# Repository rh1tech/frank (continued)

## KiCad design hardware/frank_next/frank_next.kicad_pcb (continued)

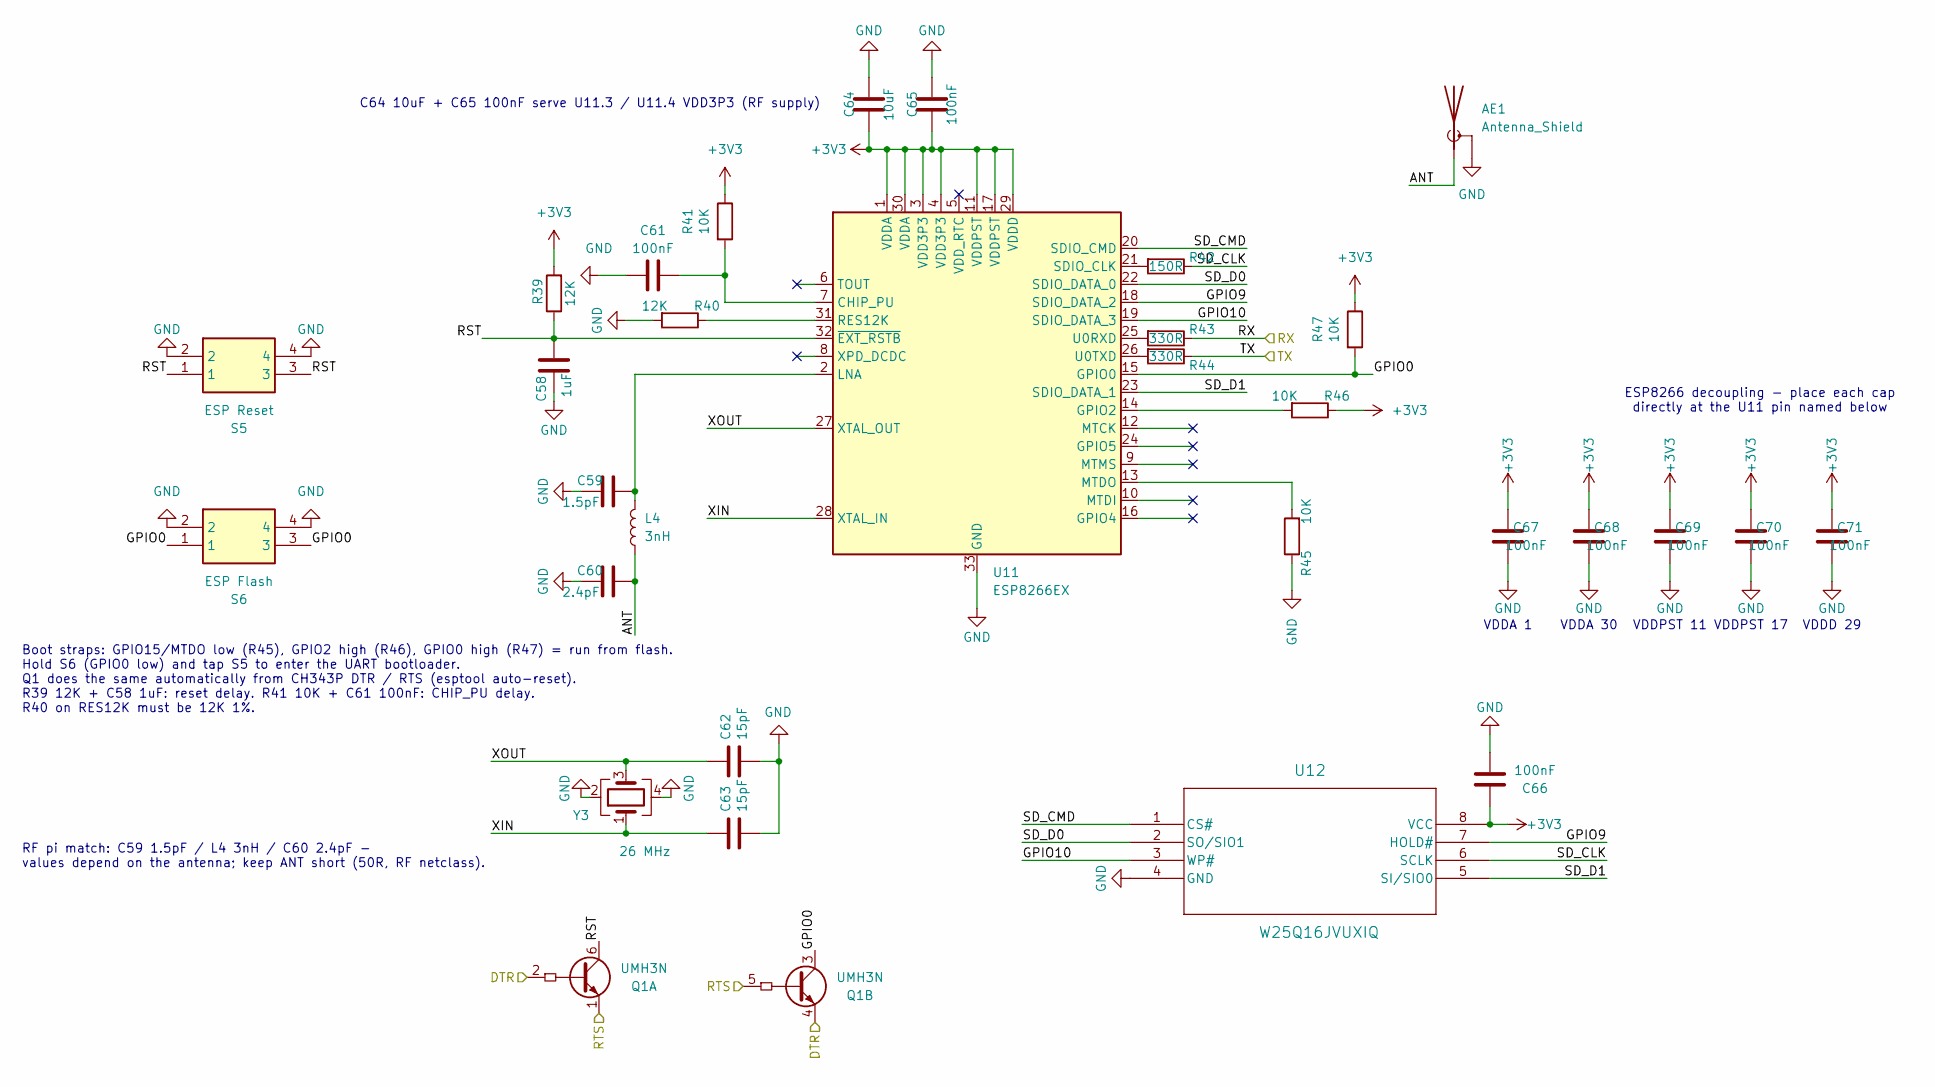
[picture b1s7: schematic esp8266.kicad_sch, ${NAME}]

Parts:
AE1: Antenna_Shield; Antenna_2.4GHz
C58: 1uF; C_0603_1608Metric; LCSC C5199872
C59: 1.5pF; C_0603_1608Metric; LCSC C1639
C60: 2.4pF; C_0603_1608Metric; LCSC C27741
C61, C65, C66, C67, C68, C69, C70, C71: 100nF; C_0603_1608Metric; LCSC C14663
C62, C63: 15pF; C_0603_1608Metric; LCSC C1644
C64: 10uF; C_0603_1608Metric; LCSC C96446
L4: 3nH; L_0603_1608Metric; LCSC C882466
Q1: UMH3N; SOT-363; LCSC C123008
R39, R40: 12K; R_0603_1608Metric; LCSC C22790
R41, R45, R46, R47: 10K; R_0603_1608Metric; LCSC C2906982
R42: 150R; R_0603_1608Metric; LCSC C22808
R43, R44: 330R; R_0603_1608Metric; LCSC C23138
S5: ESP Reset; Button_SMD_3x4x2mm; LCSC C55200587
S6: ESP Flash; Button_SMD_3x4x2mm; Mouser Part Number 611-KMR221G-LFS
U11: ESP8266EX; QFN-32-1EP_5x5mm_P0.5mm_EP3.45x3.45mm; LCSC C77967
U12: W25Q16JVUXIQ; USON-8-1EP_2x3mm_P0.5mm_EP0.2x1.6mm; LCSC C2843335
Y3: 26 MHz; Crystal_SMD_3225-4Pin_3.2x2.5mm; LCSC C15192

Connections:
+3V3: C64.2, C65.2, C66.1, C67.1, C68.1, C69.1, C70.1, C71.1, R39.2, R41.1, R46.1, R47.1, U11.1 (VDDA), U11.3 (VDD3P3), U11.4 (VDD3P3), U11.11 (VDDPST), U11.17 (VDDPST), U11.29 (VDDD), U11.30 (VDDA), U12.8 (VCC); also elsewhere on the board
/ESP8266/ANT: AE1.1 (A), C60.1, L4.1
/ESP8266/GPIO0: Q1.3 (C2), R47.2, S6.1, S6.3, U11.15 (GPIO0)
/ESP8266/GPIO9: U11.18 (SDIO_DATA_2), U12.7 (HOLD#)
/ESP8266/GPIO10: U11.19 (SDIO_DATA_3), U12.3 (WP#)
/ESP8266/RST: C58.1, Q1.6 (C1), R39.1, S5.1, S5.3, U11.32 (~EXT_RSTB)
/ESP8266/RX: R43.1; also elsewhere on the board
/ESP8266/SD_CLK: R42.1, U12.6 (SCLK)
/ESP8266/SD_CMD: U11.20 (SDIO_CMD), U12.1 (CS#)
/ESP8266/SD_D0: U11.22 (SDIO_DATA_0), U12.2 (SO/SIO1)
/ESP8266/SD_D1: U11.23 (SDIO_DATA_1), U12.5 (SI/SIO0)
/ESP8266/TX: R44.1; also elsewhere on the board
/ESP8266/XIN: C63.1, U11.28 (XTAL_IN), Y3.1
/ESP8266/XOUT: C62.1, U11.27 (XTAL_OUT), Y3.3
/ESP_DTR: Q1.2 (B1), Q1.4 (E2); also elsewhere on the board
/ESP_RTS: Q1.1 (E1), Q1.5 (B2); also elsewhere on the board
GND: AE1.2 (Shield), C58.2, C59.2, C60.2, C61.2, C62.2, C63.2, C64.1, C65.1, C66.2, C67.2, C68.2, C69.2, C70.2, C71.2, R40.2, R45.1, S5.2, S5.4, S6.2, S6.4, U11.33 (GND), U12.4 (GND), Y3.2, Y3.4; also elsewhere on the board
unnamed: C61.1, R41.2, U11.7 (CHIP_PU)
unnamed: R46.2, U11.14 (GPIO2)
unnamed: C59.1, L4.2, U11.2 (LNA)
unnamed: R45.2, U11.13 (MTDO)
unnamed: R40.1, U11.31 (RES12K)
unnamed: R42.2, U11.21 (SDIO_CLK)
unnamed: R43.2, U11.25 (U0RXD)
unnamed: R44.2, U11.26 (U0TXD)

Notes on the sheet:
VDDD 29
VDDA 30
C64 10uF + C65 100nF serve U11.3 / U11.4 VDD3P3 (RF supply)
ESP8266 decoupling - place each cap directly at the U11 pin named below
VDDPST 17
RF pi match: C59 1.5pF / L4 3nH / C60 2.4pF - values depend on the antenna; keep ANT short (50R, RF netclass).
Boot straps: GPIO15/MTDO low (R45), GPIO2 high (R46), GPIO0 high (R47) = run from flash. Hold S6 (GPIO0 low) and tap S5 to enter the UART bootloader. Q1 does the same automatically from CH343P DTR / RTS (esptool auto-reset). R39 12K + C58 1uF: reset delay. R41 10K + C61 100nF: CHIP_PU delay. R40 on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
VDDPST 11
VDDA 1

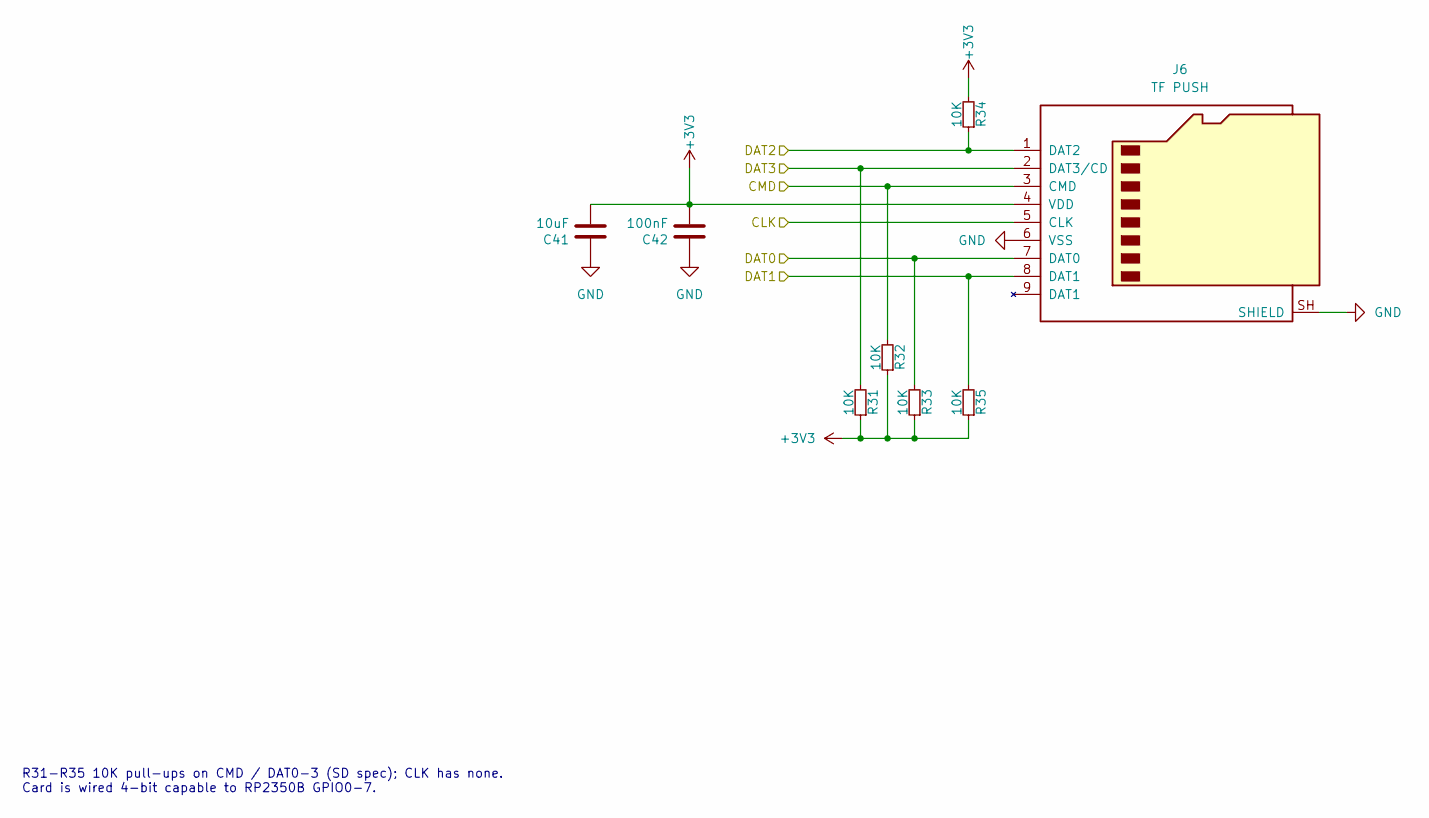
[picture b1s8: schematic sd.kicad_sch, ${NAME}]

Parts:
C41: 10uF; C_0603_1608Metric; LCSC C96446
C42: 100nF; C_0603_1608Metric; LCSC C14663
J6: TF PUSH; MicroSD_SMD_Long; LCSC C393941
R31, R32, R33, R34, R35: 10K; R_0603_1608Metric; LCSC C2906982

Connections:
+3V3: C41.2, C42.2, J6.4 (VDD), R31.1, R32.1, R33.1, R34.2, R35.1; also elsewhere on the board
/SD/CD_DAT3/GPIO7: J6.2 (DAT3/CD), R31.2; also elsewhere on the board
/SD/CLK/GPIO1: J6.5 (CLK); also elsewhere on the board
/SD/CMD/GPIO0: J6.3 (CMD), R32.2; also elsewhere on the board
/SD/DAT0/GPIO4: J6.7 (DAT0), R33.2; also elsewhere on the board
/SD/DAT1/GPIO5: J6.8 (DAT1), R35.2; also elsewhere on the board
/SD/DAT2/GPIO6: J6.1 (DAT2), R34.1; also elsewhere on the board
GND: C41.1, C42.1, J6.6 (VSS), J6.SH (SHIELD); also elsewhere on the board

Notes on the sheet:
R31-R35 10K pull-ups on CMD / DAT0-3 (SD spec); CLK has none. Card is wired 4-bit capable to RP2350B GPIO0-7.

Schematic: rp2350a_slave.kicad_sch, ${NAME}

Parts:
C21, C26, C29, C31, C32, C33, C34, C35, C36, C37, C38, C39: 100nF; C_0603_1608Metric; LCSC C14663
C22, C25, C27, C28: 4.7uF; C_0603_1608Metric; LCSC C5360844
C23, C24: 15pF; C_0603_1608Metric; LCSC C1644
C30, C40: 1uF; C_0603_1608Metric; LCSC C5199872
D2: 1N4148WS; D_SOD-323; LCSC C2128
J4: Debug; JST_SH_1x03_P1.00mm_Vertical; LCSC C160389
J5: UART; JST_SH_1x03_P1.00mm_Vertical; LCSC C160389
L2: 3.3µH; L_AOTA-B201610_2.0x1.6mm; LCSC C42411119
LD1: Blue; LED_0603_1608Metric; LCSC C965807
LD2: WS2812B-2020; LED_WS2812B-2020_PLCC4_2.0x2.0mm; LCSC C965555
R19, R30: 10K; R_0603_1608Metric; LCSC C2906982
R20, R22, R28: 1K; R_0603_1608Metric; LCSC C21190
R21: 33R; R_0603_1608Metric; LCSC C23140
R23: 0R; R_0603_1608Metric; LCSC C21189
R24: 2.2K; R_0603_1608Metric; LCSC C4190
R25, R26: 27R; R_0603_1608Metric; LCSC C25190
R27: 4.7K; R_0603_1608Metric; LCSC C23162
R29: 330R; R_0603_1608Metric; LCSC C23138
S3: RP Boot; Button_SMD_3x4x2mm; Mouser Part Number 611-KMR221G-LFS; LCSC C55200587
S4: RP Reset; Button_SMD_3x4x2mm; Mouser Part Number 611-KMR221G-LFS; LCSC C55200587
U4: W25Q128JVPIQ; WSON-8-1EP_6x5mm_P1.27mm_EP3.45x4.35mm; Mouser Part Number 454-W25Q128JVPIQ; LCSC C190862
U5: RP2350; QFN-60-1EP_7x7mm_P0.4mm_EP3.4x3.4mm; LCSC C42411118
U6, U8: APS6404L-3SQR-ZR; PSON50P200X300X50-9N; PARTREV 2.3; LCSC C3040877
U7: SN74LVC1G3157DBVR; SOT-23-6; LCSC C10426
Y2: 12 MHz; Crystal_SMD_3225-4Pin_3.2x2.5mm; LCSC C20625731

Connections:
+1V1_A: C25.1, C26.1, C28.1, C29.1, L2.1, U5.6 (DVDD), U5.23 (DVDD), U5.39 (DVDD), U5.50 (VREG_FB)
+3V3: C21.1, C22.1, C30.2, C31.1, C32.1, C33.1, C34.1, C35.1, C36.1, C37.1, C39.1, C40.1, R19.2, R21.1, R24.2, R30.1, U4.8 (VCC), U5.1 (IOVDD), U5.11 (IOVDD), U5.20 (IOVDD), U5.30 (IOVDD), U5.38 (IOVDD), U5.44 (ADC_AVDD), U5.45 (IOVDD), U5.49 (VREG_VIN), U5.53 (USB_OTP_VDD), U5.54 (QSPI_IOVDD), U6.8 (VDD), U7.5 (VCC), U8.8 (VDD); also elsewhere on the board
/RP2350A/BOOT: R22.2, S3.1, S3.3
/RP2350A/D+: R25.1; also elsewhere on the board
/RP2350A/D-: R26.1; also elsewhere on the board
/RP2350A/GPIO0: U5.2 (GPIO0), U7.4 (A)
/RP2350A/GPIO9: U5.13 (GPIO9); also elsewhere on the board
/RP2350A/GPIO24/UART_1: J5.1, U5.36 (GPIO24)
/RP2350A/GPIO25/UART_3: J5.3, U5.37 (GPIO25)
/RP2350A/GPIO28: R27.1, U5.42 (GPIO28_ADC2), U7.6 (S)
/RP2350A/GPIO29: U5.43 (GPIO29_ADC3)
/RP2350A/PSRAM0_CS: R24.1, U6.1 (~CE), U7.3 (B1)
/RP2350A/PSRAM1_CS: R30.2, U7.1 (B2), U8.1 (~CE)
/RP2350A/QSPI_SCLK: U4.6 (CLK), U5.56 (QSPI_SCLK), U6.6 (SCLK), U8.6 (SCLK)
/RP2350A/QSPI_SD0: U4.5 (DI_(IO0)), U5.57 (QSPI_SD0), U6.5 (SI/SIO(0)), U8.5 (SI/SIO(0))
/RP2350A/QSPI_SD1: U4.2 (DO_(IO1)), U5.59 (QSPI_SD1), U6.2 (SO/SIO(1)), U8.2 (SO/SIO(1))
/RP2350A/QSPI_SD2: U4.3 (~WP_(IO2)), U5.58 (QSPI_SD2), U6.3 (SIO(2)), U8.3 (SIO(2))
/RP2350A/QSPI_SD3: U4.7 (~HOLD_OR_/RESET_(IO3)), U5.55 (QSPI_SD3), U6.7 (SIO(3)), U8.7 (SIO(3))
/RP2350A/QSPI_SS: R22.1, R23.1, U5.60 (QSPI_SS)
/RP2350A/SWCLK: J4.3, U5.24 (SWCLK)
/RP2350A/SWD: J4.1, U5.25 (SWD)
/RP2350A/VREG_AVDD: C27.1, R21.2, U5.46 (VREG_AVDD)
/RP2350A/VREG_LX: L2.2, U5.48 (VREG_LX)
/RP2350A/XIN: C23.1, U5.21 (XIN), Y2.3
/RP2350A/XOUT: R20.2, U5.22 (XOUT)
/RP2350/20B/1A/D0: U5.3 (GPIO1); also elsewhere on the board
/RP2350/21B/2A/D1: U5.4 (GPIO2); also elsewhere on the board
/RP2350/22B/3A/D2: U5.5 (GPIO3); also elsewhere on the board
/RP2350/23B/4A/D3: U5.7 (GPIO4); also elsewhere on the board
/RP2350/24B/5A/D4: U5.8 (GPIO5); also elsewhere on the board
/RP2350/25B/6A/D5: U5.9 (GPIO6); also elsewhere on the board
/RP2350/26B/7A/D6: U5.10 (GPIO7); also elsewhere on the board
/RP2350/27B/8A/D7: U5.12 (GPIO8); also elsewhere on the board
/RP2350/29B/10A/VALID: U5.14 (GPIO10); also elsewhere on the board
/RP2350/30B/11A/D0: U5.15 (GPIO11); also elsewhere on the board
/RP2350/31B/12A/D1: U5.16 (GPIO12); also elsewhere on the board
/RP2350/32B/13A/D2: U5.17 (GPIO13); also elsewhere on the board
/RP2350/33B/14A/D3: U5.18 (GPIO14); also elsewhere on the board
/RP2350/34B/15A/D4: U5.19 (GPIO15); also elsewhere on the board
/RP2350/35B/16A/D5: U5.27 (GPIO16); also elsewhere on the board
/RP2350/36B/17A/D6: U5.28 (GPIO17); also elsewhere on the board
/RP2350/37B/18A/D7: U5.29 (GPIO18); also elsewhere on the board
/RP2350/38B/19A/CLK: U5.31 (GPIO19); also elsewhere on the board
/RP2350/39B/20A/VALID: U5.32 (GPIO20); also elsewhere on the board
/RP2350/40B/21A/FS: U5.33 (GPIO21); also elsewhere on the board
/RP2350/41B/22A/DB_MS: U5.34 (GPIO22); also elsewhere on the board
/RP2350/42B/23A/DB_SM: U5.35 (GPIO23); also elsewhere on the board
/RP2350/43B/RUNA/SR: S4.1, S4.3, U5.26 (RUN); also elsewhere on the board
GND: C21.2, C22.2, C23.2, C24.2, C25.2, C26.2, C27.2, C28.2, C29.2, C30.1, C31.2, C32.2, C33.2, C34.2, C35.2, C36.2, C37.2, C38.2, C39.2, C40.2, J4.2, J5.2, LD1.1 (K), LD2.2 (VSS), R27.2, S3.2, S3.4, S4.2, S4.4, U4.4 (GND_1), U4.9 (GND_2), U5.47 (VREG_PGND), U5.61 (GND), U6.4 (VSS), U6.9 (EXP), U7.2 (GND), U8.4 (VSS), U8.9 (EXP), Y2.2, Y2.4; also elsewhere on the board
unnamed: C24.1, R20.1, Y2.1
unnamed: C38.1, D2.1 (K), LD2.4 (VDD)
unnamed: LD1.2 (A), R28.1
unnamed: LD2.3 (DIN), R29.1
unnamed: R19.1, R23.2, U4.1 (~CS)
unnamed: R28.2, U5.40 (GPIO26_ADC0)
unnamed: R29.2, U5.41 (GPIO27_ADC1)
unnamed: R26.2, U5.51 (USB_DM)
unnamed: R25.2, U5.52 (USB_DP)
VBUS: D2.2 (A); also elsewhere on the board

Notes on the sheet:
44+45
LD2 WS2812B is powered from VBUS via D2 (~4.4 V), so the 3.3 V DIN still meets its VIH. R29 330R: data series.
PSRAM bank: GPIO28 L (default, R27 4.7k) = U6, H = U8. Flush XIP cache before switching banks.
Core supply: L2 3.3uH + C22 / C25 4.7uF = on-chip buck, keep the loop short. R21 33R + C27 4.7uF filter VREG_AVDD.
Make sure these are close to RP2350
S3 BOOT: QSPI_SS low via R22 1K. RUN comes from RP2350B (root sheet).
53+54

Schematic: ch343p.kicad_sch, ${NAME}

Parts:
C97, C98, C99: 100nF; C_0603_1608Metric; LCSC C14663
LD4: Orange; LED_0603_1608Metric; LCSC C965800
R70: 1K; R_0603_1608Metric; LCSC C21190
U22: CH343P; WCH_QFN-16-1EP_3x3mm_P0.5mm_EP1.8x1.8mm; LCSC C2846043

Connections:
+3V3: C99.2, R70.2, U22.1 (VIO); also elsewhere on the board
/CH343P/UD+: U22.7 (UD+); also elsewhere on the board
/CH343P/UD-: U22.8 (UD-); also elsewhere on the board
/ESP_DTR: U22.12 (~DTR); also elsewhere on the board
/ESP_RTS: U22.13 (~RTS); also elsewhere on the board
/TTL_RXD: U22.5 (RXD); also elsewhere on the board
/TTL_TXD: U22.4 (TXD); also elsewhere on the board
GND: C97.1, C98.1, C99.1, U22.2 (GND), U22.17 (GND_EPAD); also elsewhere on the board
unnamed: LD4.2 (A), R70.1
unnamed: LD4.1 (K), U22.10 (~ACT)
unnamed: C98.2, U22.6 (V3_{OUT})
VBUS: C97.2, U22.3 (VDD5), U22.9 (VBUS); also elsewhere on the board

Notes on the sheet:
CH343P USB-UART: reached from J11 when USB_SEL is low. Talks to the ESP8266 through the ESP Mux (UART_SEL low); DTR / RTS drive the ESP8266 auto-program transistors (Q1). LD4: activity LED.

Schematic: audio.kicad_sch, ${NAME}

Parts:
C43, C44, C50, C53, C55: 100nF; C_0603_1608Metric; LCSC C14663
C45, C46, C49, C51, C52, C54, C56: 10uF; C_0603_1608Metric; LCSC C96446
C47, C48: 100uF; C_1206_3216Metric; LCSC C7432784
C57: 1uF; C_0603_1608Metric; LCSC C5199872
J7: PJ-320D; AudioJack_3.5mm_PJ320D_AudioOut; LCSC C431535
J8: Speaker; JST_GH_1x02_P1.25mm; LCSC C114130
L3: 330R 2A; L_0805_2012Metric; LCSC C76819
R36, R37: 4.7K; R_0603_1608Metric; LCSC C23162
R38: 10K; R_0603_1608Metric; LCSC C2906982
U9: TLV320DAC3100IRHBR; Mouser Part Number 595-V320DAC3100IRHBR; LCSC C179677
U10: XC6206P182MR-G; Mouser Part Number 865-XC6206P182MR-G; LCSC C347373

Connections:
+1V8: C44.2, C56.2, U9.3 (DVDD), U10.2 (VOUT)
+3V3: C43.1, C45.1, C49.2, C50.2, C51.2, C53.2, C57.2, R36.2, R37.2, R38.2, U9.2 (IOVDD), U9.17 (AVDD), U9.28 (HPVDD), U10.3 (VIN); also elsewhere on the board
/Audio/+5V_SPK: C52.2, C54.2, C55.2, L3.1, U9.21 (SPKVDD_1), U9.24 (SPKVDD_2)
/Audio/SPKM: J8.2, U9.19 (SPKM_1), U9.23 (SPKM_2)
/Audio/SPKP: J8.1, U9.22 (SPKP_1), U9.26 (SPKP_2)
/GPIO2/SDA: R37.1, U9.9 (SDA); also elsewhere on the board
/GPIO3/SCL: R36.1, U9.10 (SCL); also elsewhere on the board
/GPIO8/MCLK: U9.8 (MCLK); also elsewhere on the board
/GPIO9/BCLK: U9.7 (BCLK); also elsewhere on the board
/GPIO10/WCLK: U9.6 (WCLK); also elsewhere on the board
/GPIO11/DIN: U9.5 (DIN); also elsewhere on the board
GND: C43.2, C44.1, C45.2, C46.2, C49.1, C50.1, C51.1, C52.1, C53.1, C54.1, C55.1, C56.1, C57.1, J7.S, U9.1 (IOVSS), U9.16 (AVSS), U9.18 (DVSS), U9.20 (SPKVSS_1), U9.25 (SPKVSS_2), U9.29 (HPVSS), U9.33 (EP), U10.1 (VSS); also elsewhere on the board
unnamed: C47.1, J7.R
unnamed: C48.1, J7.T
unnamed: C48.2, U9.27 (HPL)
unnamed: C47.2, U9.30 (HPR)
unnamed: C46.1, R38.1, U9.31 (~RESET)
VBUS: L3.2; also elsewhere on the board

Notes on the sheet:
U9 TLV320DAC3100, I2C address 0x18 on GPIO2 / GPIO3 (shared with RTC U13, R36 / R37 4.7K pull-ups). I2S: MCLK GPIO8, BCLK GPIO9, WCLK GPIO10, DIN GPIO11. DVDD 1.8 V from U10 XC6206 LDO. SPKVDD from VBUS through L3 ferrite; C55 / C52 / C54 at the SPKVDD pins. Headphone HPL / HPR AC-coupled by C47 / 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

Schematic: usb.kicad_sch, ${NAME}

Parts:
C76, C79, C80, C86, C88: 100nF; C_0603_1608Metric; LCSC C14663
C77, C78: 100uF; CP_Elec_6.3x6.0; LCSC C19270701
C81, C82, C83, C85, C87, C89, C91, C92, C93: 10uF; C_0603_1608Metric; LCSC C96446
C84: 47nF; C_0603_1608Metric; LCSC C1622
C90: 1uF; C_0603_1608Metric; LCSC C5199872
C94, C95: 12pF; C_0603_1608Metric; LCSC C107034
C96: 22pF; C_0603_1608Metric; LCSC C1653
J10, J11: USB4215-03-A; USB_C_Receptacle; LCSC C37616412
JP4: USB Debug; SolderJumper-2_P1.3mm_Open_RoundedPad1.0x1.5mm
JP5: PWR Debug; SolderJumper-2_P1.3mm_Open_RoundedPad1.0x1.5mm
L5: 330R 2A; L_0805_2012Metric; LCSC C76819
L6: 2.2uH; L_Cenker_CKCS3015; LCSC C167747
LD3: Green; LED_0603_1608Metric; LCSC C965804
R55, R65: 10K; R_0603_1608Metric; LCSC C2906982
R56, R57, R58, R59: 5.1K; R_0603_1608Metric; LCSC C23186
R60: 300K; R_0603_1608Metric; LCSC C23024
R61, R64, R68: 100K; R_0603_1608Metric; LCSC C25803
R62: 1M; R_0603_1608Metric; LCSC C22935; not fitted
R63: 1K; R_0603_1608Metric; LCSC C21190
R66, R69: 22K; R_0603_1608Metric; LCSC C31850
R67: 4.7K; R_0603_1608Metric; LCSC C23162; not fitted
S7: SS12D01; Switch_Slide_SS12D00; Mouser Part Number 611-SK12D07VG3NS
S8: SK12D07VG3NS; Switch_Slide_SK12D07VG3NS_PWR; Mouser Part Number 611-SK12D07VG3NS; LCSC C431547
U14, U19: TS3USB221RSER; UQFN-10; LCSC C130085
U15, U16: TPD4S012DRYR; Mouser Part Number 595-TPD4S012DRYR; LCSC C96506
U17: TPS2116DRL; SOT-583-8; LCSC C3235557
U18: AO3401A; SOT-23-3L_AOS; LCSC C15127
U20: SY8089AAAC; SOT-23-5; LCSC C78988
U21: CH334F; QFN-24-1EP_4x4mm_P0.5mm_EP2.7x2.7mm; LCSC C5187527
Y4: 12 MHz; Crystal_SMD_3225-4Pin_3.2x2.5mm; LCSC C20625731

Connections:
+3V3: C76.1, C86.2, C91.1, C92.1, C96.1, JP4.1 (A), L6.1, R55.1, R63.2, R68.1, S7.2, U14.10 (VCC), U19.10 (VCC); also elsewhere on the board
/CH343P/UD+: U14.1 (1D+); also elsewhere on the board
/CH343P/UD-: U14.2 (1D-); also elsewhere on the board
/RP2350A/D+: U14.3 (2D+); also elsewhere on the board
/RP2350A/D-: U14.4 (2D-); also elsewhere on the board
/RP2350B/D+: U19.8 (D+); also elsewhere on the board
/RP2350B/D-: U19.7 (D-); also elsewhere on the board
/USB/+5V_BUCK: C85.1, C87.1, C88.1, L5.2, U20.1 (EN), U20.4 (IN)
/USB/D2+: J10.6 (DP1), J10.8 (DP2), U15.1 (D+), U19.1 (1D+)
/USB/D2-: J10.5 (DN2), J10.7 (DN1), U15.2 (D-_), U19.2 (1D-)
/USB/DH+: U19.3 (2D+), U21.15 (DPU+)
/USB/DH-: U19.4 (2D-), U21.14 (DMU-)
/USB/DS1+: U21.12 (DP1+); also elsewhere on the board
/USB/DS1-: U21.11 (DM1-); also elsewhere on the board
/USB/DS2+: U21.10 (DP2+); also elsewhere on the board
/USB/DS2-: U21.9 (DM2-); also elsewhere on the board
/USB/DS3+: U21.8 (DP3+); also elsewhere on the board
/USB/DS3-: U21.7 (DM3-); also elsewhere on the board
/USB/OVCUR: U21.1 (~OVCUR); also elsewhere on the board
/USB/PWREN: U21.24 (~PWREN); also elsewhere on the board
/USB/S: JP4.2 (B), R65.2, S7.3, U19.9 (S)
/USB/ST: R62.2, U17.8 (ST)
/USB/USBC_D+: J11.6 (DP1), J11.8 (DP2), U14.8 (D+), U16.1 (D+)
/USB/USBC_D-: J11.5 (DN2), J11.7 (DN1), U14.7 (D-), U16.2 (D-_)
/USB/VBUS_IN: C83.1, R64.2, U17.2 (VOUT), U17.7 (VOUT), U18.2 (S)
/USB/VBUS_IN1: C79.2, C81.2, J11.2 (VBUS), J11.11 (VBUS), R60.2, U16.6 (VBUS), U17.3 (VIN1), U17.5 (MODE)
/USB/VBUS_IN2: C80.2, C82.2, J10.2 (VBUS), J10.11 (VBUS), U15.6 (VBUS), U17.6 (VIN2)
/USB/VDD33: C89.2, C90.2, U21.20 (VDD33_{LDO})
/USB/XTAL_N: C94.1, U21.3 (XO), Y4.3
/USB/XTAL_P: C95.1, U21.4 (XI), Y4.1
/USB_SEL: R55.2, U14.9 (S); also elsewhere on the board
GND: C76.2, C77.2, C78.2, C79.1, C80.1, C81.1, C82.1, C83.2, C85.2, C86.1, C87.2, C88.2, C89.1, C90.1, C91.2, C92.2, C93.1, C94.2, C95.2, J10.1 (GND), J10.12 (GND), J10.13 (SHIELD), J11.1 (GND), J11.12 (GND), J11.13 (SHIELD), JP5.1 (A), LD3.1 (K), R56.1, R57.1, R58.1, R59.1, R61.1, R65.1, R67.2, R69.2, S8.2, U14.5 (GND), U14.6 (~OE), U15.4 (GND), U16.4 (GND), U17.1 (GND), U19.5 (GND), U19.6 (~OE), U20.2 (GND), U21.25 (GND), Y4.2, Y4.4; also elsewhere on the board
unnamed: J10.4 (CC1), R56.2
unnamed: J10.10 (CC2), R57.2
unnamed: J11.4 (CC1), R58.2
unnamed: J11.10 (CC2), R59.2
unnamed: JP5.2 (B), R66.2, S8.3
unnamed: LD3.2 (A), R63.1
unnamed: R60.1, R61.2, R62.1, U17.4 (PR1)
unnamed: C84.1, R64.1, R66.1, U18.1 (G)
unnamed: C96.2, R68.2, R69.1, U20.5 (FB)
unnamed: L6.2, U20.3 (LX)
unnamed: R67.1, U21.18 (PSELF)
VBUS: C77.1, C78.1, C84.2, C93.2, L5.1, U18.3 (D), U21.19 (V5); also elsewhere on the board

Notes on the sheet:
USB data: U14 (USB_SEL): J11 -> RP2350A (H) or CH343P (L). U19 (S7 USB FUNC, JP4 forces H): RP2350B -> J10 (L, device) or CH334F hub upstream -> USB-A ports (H, host).
Power path: J11 (VIN1) / J10 (VIN2) -> U17 TPS2116. J11 is preferred while its VBUS is above ~4 V (R60 / R61 on PR1, MODE tied to VIN1). R62: DNP. S8 -> U18 AO3401A P-FET: R64 holds it off, S8 pulls the gate low via R66, C84 = soft start. JP5 bypasses S8. VBUS -> L5 ferrite -> U20 SY8089 buck: 3V3 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
USB-A shared VBUS bulk: C77 + C78 = 200 uF USB 2.0 7.2.4.1: >= 120 uF per hub, may be shared DMBJ JBLM2101M016C058RTM (LCSC C19270701) 100 uF 16 V aluminium polymer, ESR 40 mOhm
5.1K CC pull-downs (Rd): both USB-C ports are sinks

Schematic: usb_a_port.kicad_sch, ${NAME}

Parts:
C100: 100nF; C_0603_1608Metric; LCSC C14663
C101: 10uF; C_0603_1608Metric; LCSC C96446
J12: AF 10.0 HC6.3; USB_A_Short; LCSC C456017
R71: 100K; R_0603_1608Metric; LCSC C25803
U23: TPD4S012DRYR; Mouser Part Number 595-TPD4S012DRYR; LCSC C96506
U24: CH217A; SOT-23-6; LCSC C54973763

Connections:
/USB/DS1+: J12.3 (D+), U23.1 (D+); also elsewhere on the board
/USB/DS1-: J12.2 (D-), U23.2 (D-_); also elsewhere on the board
/USB/OVCUR: U24.3 (FLAG#); also elsewhere on the board
/USB/PWREN: U24.4 (EN#); also elsewhere on the board
/USB/USB A Port 1/VBUS_P: C100.1, J12.1 (VBUS), U23.6 (VBUS), U24.1 (VOUT)
GND: C100.2, C101.1, J12.4 (GND), J12.5 (Shield), R71.1, U23.4 (GND), U24.2 (GND); also elsewhere on the board
unnamed: R71.2, U24.5 (ISET)
VBUS: C101.2, U24.6 (VIN); also elsewhere on the board

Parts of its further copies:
C102, C104: 100nF; C_0603_1608Metric; LCSC C14663
C103, C105: 10uF; C_0603_1608Metric; LCSC C96446
J13, J14: AF 10.0 HC6.3; USB_A_Short; LCSC C456017
R72, R73: 100K; R_0603_1608Metric; LCSC C25803
U25, U27: TPD4S012DRYR; Mouser Part Number 595-TPD4S012DRYR; LCSC C96506
U26, U28: CH217A; SOT-23-6; LCSC C54973763

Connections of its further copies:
/USB/DS2+: J13.3 (D+), U25.1 (D+); also elsewhere on the board
/USB/DS2-: J13.2 (D-), U25.2 (D-_); also elsewhere on the board
/USB/DS3+: J14.3 (D+), U27.1 (D+); also elsewhere on the board
/USB/DS3-: J14.2 (D-), U27.2 (D-_); also elsewhere on the board
/USB/OVCUR: U26.3 (FLAG#), U28.3 (FLAG#); also elsewhere on the board
/USB/PWREN: U26.4 (EN#), U28.4 (EN#); also elsewhere on the board
/USB/USB A Port 2/VBUS_P: C102.1, J13.1 (VBUS), U25.6 (VBUS), U26.1 (VOUT)
/USB/USB A Port 3/VBUS_P: C104.1, J14.1 (VBUS), U27.6 (VBUS), U28.1 (VOUT)
GND: C102.2, C103.1, C104.2, C105.1, J13.4 (GND), J13.5 (Shield), J14.4 (GND), J14.5 (Shield), R72.1, R73.1, U25.4 (GND), U26.2 (GND), U27.4 (GND), U28.2 (GND); also elsewhere on the board
unnamed: R72.2, U26.5 (ISET)
unnamed: R73.2, U28.5 (ISET)
VBUS: C103.2, C105.2, U26.6 (VIN), U28.6 (VIN); also elsewhere on the board

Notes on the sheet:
CH217A: current-limited VBUS switch for this port, enabled by the hub PWREN, over-current reported on OVCUR. The ISET resistor sets the limit. TPD4S012: ESD protection for D+ / D- / VBUS.

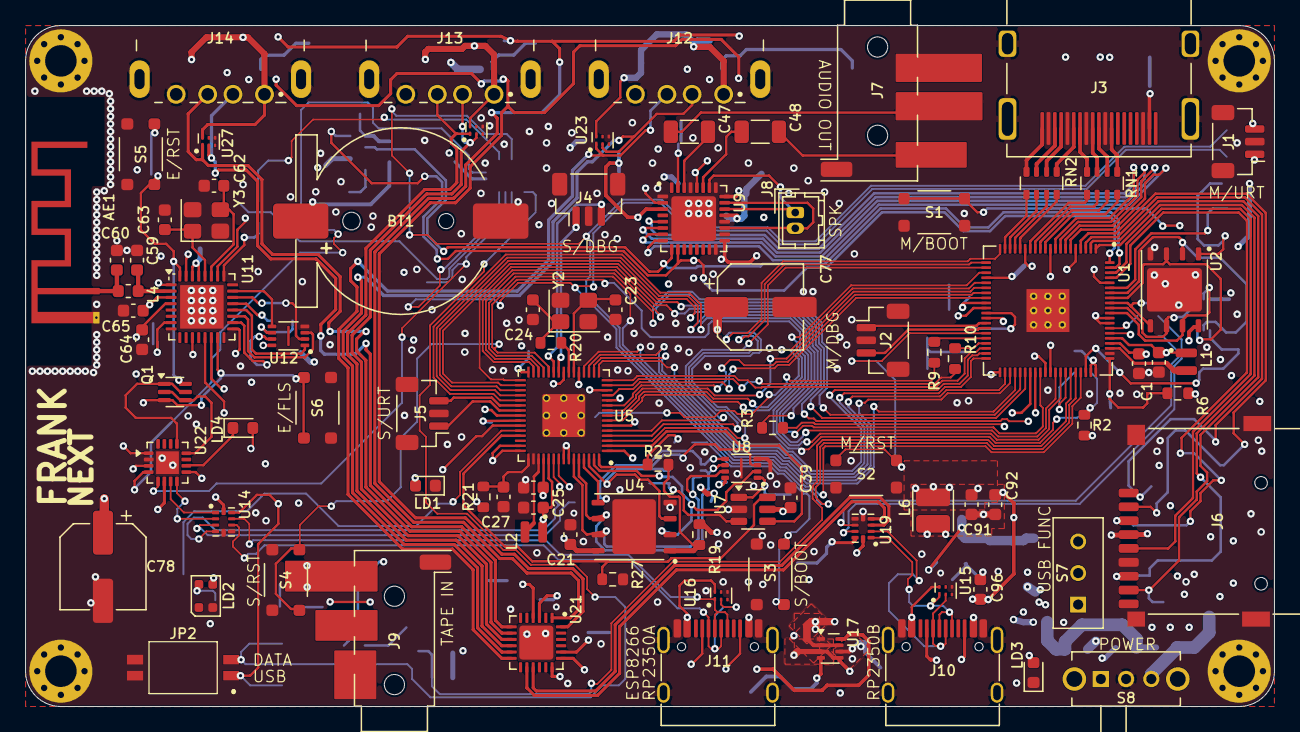
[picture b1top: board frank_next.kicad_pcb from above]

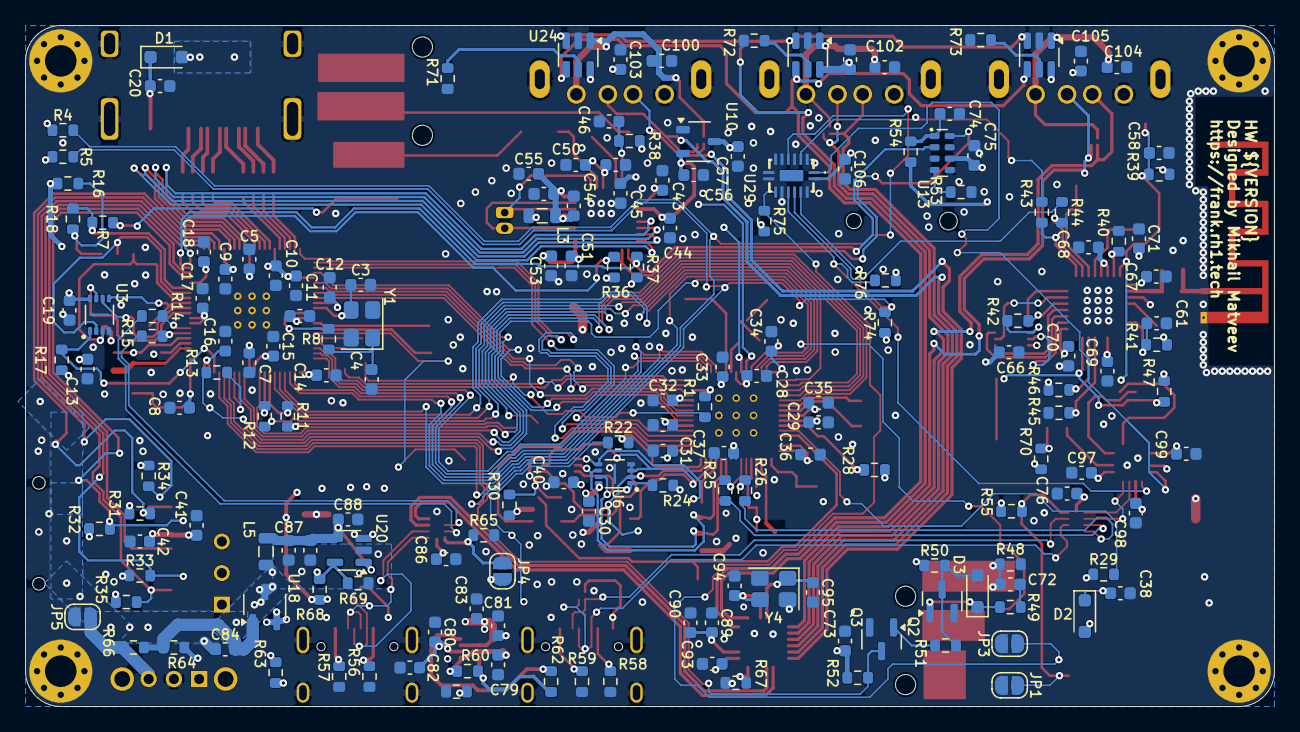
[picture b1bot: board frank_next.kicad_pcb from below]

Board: 4 copper layers, 99.0 x 54.0 mm, 266 parts (173 on the bottom side), 210 nets.

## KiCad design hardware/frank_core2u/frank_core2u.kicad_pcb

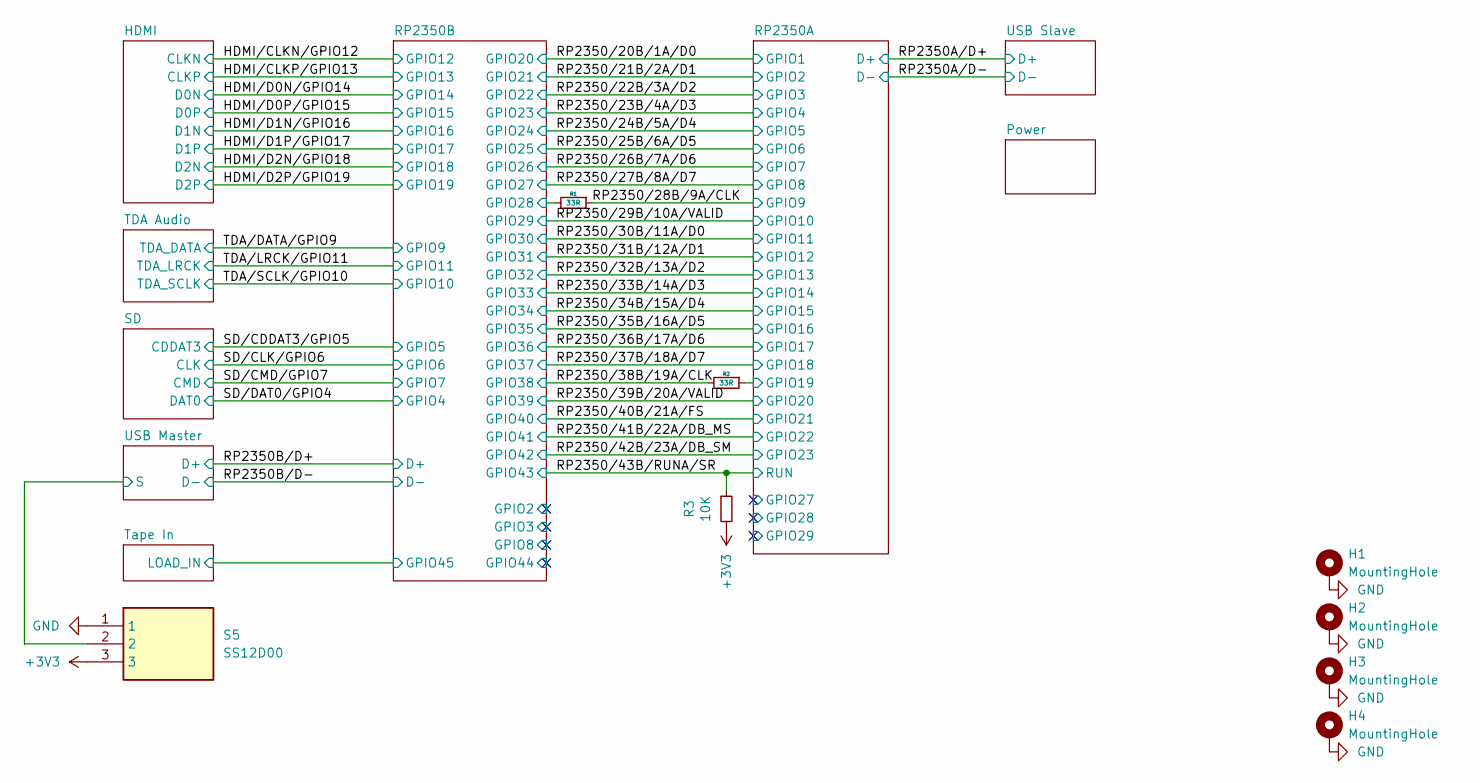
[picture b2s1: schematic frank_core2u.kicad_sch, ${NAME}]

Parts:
H1, H2, H3, H4: MountingHole; MountingHole_2.5mm_Pad_Via
R1, R2: 33R; R_0603_1608Metric
R3: 10K; R_0603_1608Metric
S5: SS12D00; Switch_Slide_SS12D00; Mouser Part Number 611-SK12D07VG3NS

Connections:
+3V3: R3.2, S5.3; also elsewhere on the board
/RP2350A/GPIO19: R2.1; also elsewhere on the board
/RP2350B/GPIO28: R1.2; also elsewhere on the board
/RP2350/28B/9A/CLK: R1.1; also elsewhere on the board
/RP2350/38B/19A/CLK: R2.2; also elsewhere on the board
/RP2350/43B/RUNA/SR: R3.1; also elsewhere on the board
/USB Master/S: S5.2; also elsewhere on the board
GND: H1.1 (1_1), H2.1 (1_1), H3.1 (1_1), H4.1 (1_1), S5.1; also elsewhere on the board

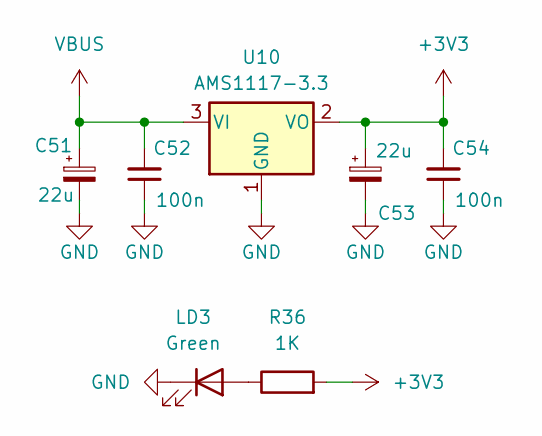
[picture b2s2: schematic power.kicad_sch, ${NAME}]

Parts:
C51, C53: 22u; CP_EIA-3528-12_Kemet-T
C52, C54: 100n; C_0603_1608Metric
LD3: Green; LED_0603_1608Metric
R36: 1K; R_0603_1608Metric
U10: AMS1117-3.3; SOT-89-3

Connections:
+3V3: C53.1, C54.2, R36.2, U10.2 (VO); also elsewhere on the board
GND: C51.2, C52.1, C53.2, C54.1, LD3.1 (K), U10.1 (GND); also elsewhere on the board
unnamed: LD3.2 (A), R36.1
VBUS: C51.1, C52.2, U10.3 (VI); also elsewhere on the board

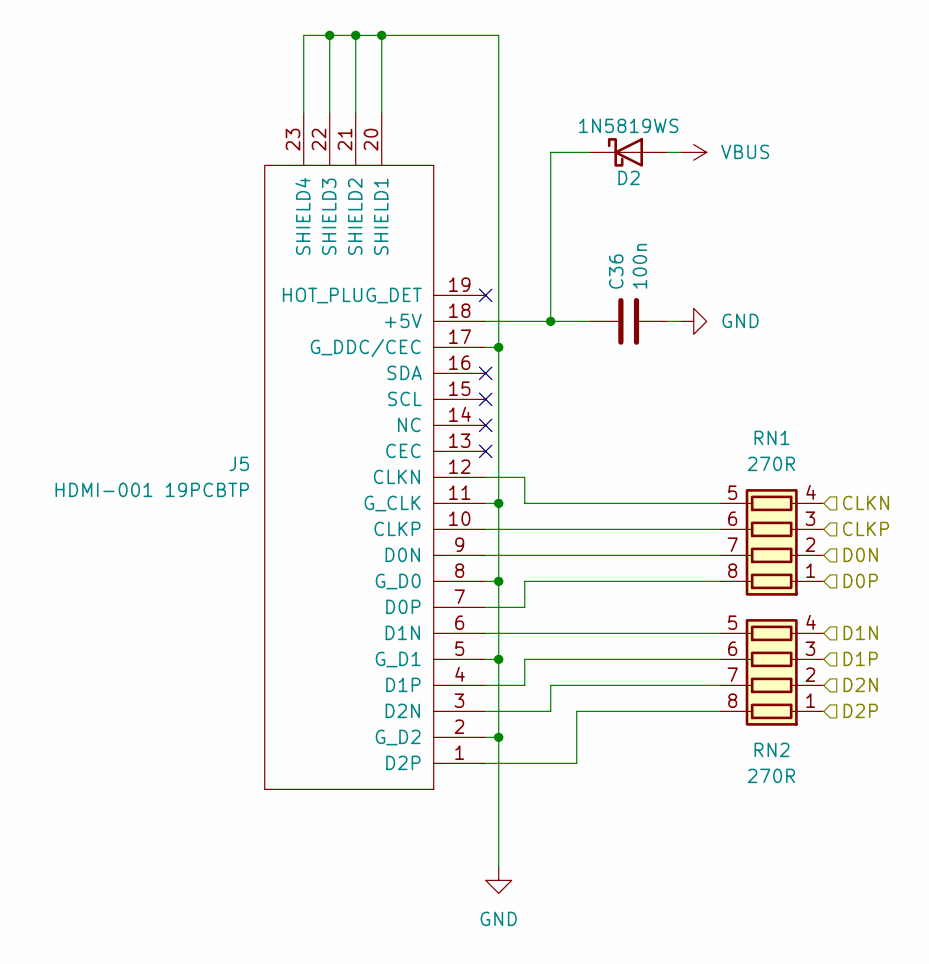
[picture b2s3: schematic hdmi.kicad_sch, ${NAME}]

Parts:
C36: 100n; C_0603_1608Metric
D2: 1N5819WS; D_SOD-323
J5: HDMI-001 19PCBTP; HDMI_Female; LCSC C138388
RN1, RN2: 270R; R_Array_4x0603

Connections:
/HDMI/CLKN/GPIO12: RN1.4 (R4.1); also elsewhere on the board
/HDMI/CLKP/GPIO13: RN1.3 (R3.1); also elsewhere on the board
/HDMI/D0N/GPIO14: RN1.2 (R2.1); also elsewhere on the board
/HDMI/D0P/GPIO15: RN1.1 (R1.1); also elsewhere on the board
/HDMI/D1N/GPIO16: RN2.4 (R4.1); also elsewhere on the board
/HDMI/D1P/GPIO17: RN2.3 (R3.1); also elsewhere on the board
/HDMI/D2N/GPIO18: RN2.2 (R2.1); also elsewhere on the board
/HDMI/D2P/GPIO19: RN2.1 (R1.1); also elsewhere on the board
GND: C36.2, J5.2 (G_D2), J5.5 (G_D1), J5.8 (G_D0), J5.11 (G_CLK), J5.17 (G_DDC/CEC), J5.20 (SHIELD1), J5.21 (SHIELD2), J5.22 (SHIELD3), J5.23 (SHIELD4); also elsewhere on the board
unnamed: C36.1, D2.1 (K), J5.18 (+5V)
unnamed: J5.12 (CLKN), RN1.5 (R4.2)
unnamed: J5.10 (CLKP), RN1.6 (R3.2)
unnamed: J5.9 (D0N), RN1.7 (R2.2)
unnamed: J5.7 (D0P), RN1.8 (R1.2)
unnamed: J5.6 (D1N), RN2.5 (R4.2)
unnamed: J5.4 (D1P), RN2.6 (R3.2)
unnamed: J5.3 (D2N), RN2.7 (R2.2)
unnamed: J5.1 (D2P), RN2.8 (R1.2)
VBUS: D2.2 (A); also elsewhere on the board

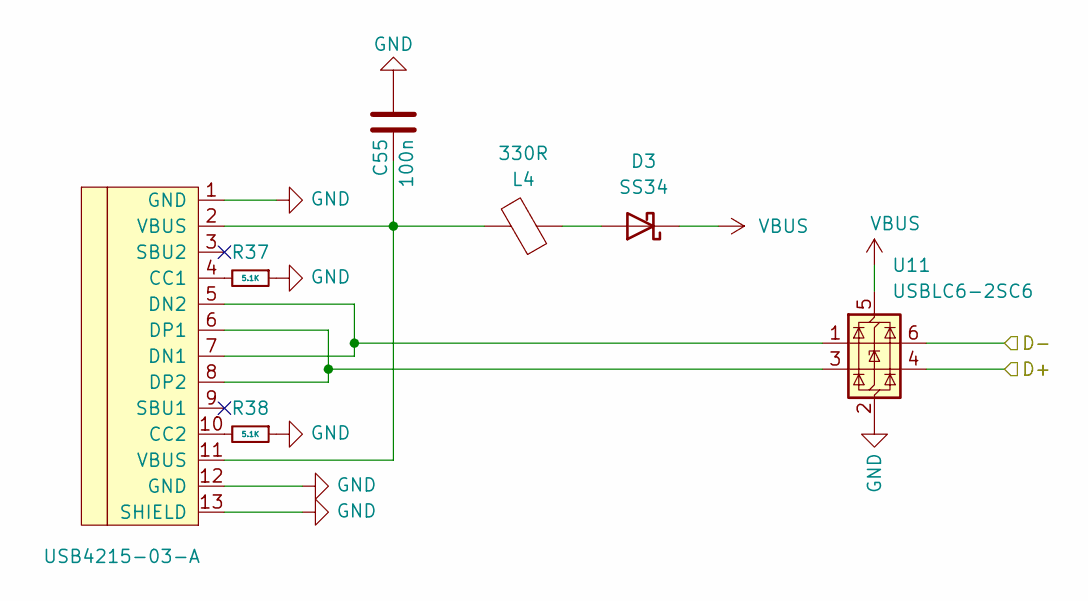
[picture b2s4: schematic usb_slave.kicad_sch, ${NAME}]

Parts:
C55: 100n; C_0603_1608Metric
D3: SS34; D_SMA
J11: USB4215-03-A; USB_C_Receptacle; LCSC C165948
L4: 330R; L_0603_1608Metric
R37, R38: 5.1K; R_0603_1608Metric
U11: USBLC6-2SC6; SOT-23-6

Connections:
/RP2350A/D+: U11.4 (I/O2); also elsewhere on the board
/RP2350A/D-: U11.6 (I/O1); also elsewhere on the board
GND: C55.2, J11.1 (GND), J11.12 (GND), J11.13 (SHIELD), R37.1, R38.1, U11.2 (GND); also elsewhere on the board
unnamed: C55.1, J11.2 (VBUS), J11.11 (VBUS), L4.2
unnamed: D3.2 (A), L4.1
unnamed: J11.4 (CC1), R37.2
unnamed: J11.10 (CC2), R38.2
unnamed: J11.5 (DN2), J11.7 (DN1), U11.1 (I/O1)
unnamed: J11.6 (DP1), J11.8 (DP2), U11.3 (I/O2)
VBUS: D3.1 (K), U11.5 (VBUS); also elsewhere on the board
